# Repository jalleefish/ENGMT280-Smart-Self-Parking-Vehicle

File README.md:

# ENGMT280-Smart-Self-Parking-Vehicle
ENGMT280/ENGEE281 – 25B
Smart Self-parking Vehicle – Design Rules
A scaled version of a typical car park layout will be setup in D.2.03 and C.1.12 (eventually). So
please make sure to feel free to switch lab spaces during the later half of the trimester to have a
go at testing your systems on the track. Below are the design requirements and design constraints
that needs to met by the Smart self-parking vehicle (SSV) you design, while meeting the event
regulations.

Fig. 1(top). Arena for the SSV showing the starting point and the parking bays and (bottom)
Colored tiles placed at the parking bay’s rear wall and parking sensors to check successful vehicle
parking.
ENGMT280/ENGEE281 – 25B
1. Your SAV, once ‘started’, should be able to complete the task autonomously – i.e., no user
inputs from any sort of wired or wireless communication sources once the SSV starts to move.
2. The only form of external communication once your SSV starts is the camera feed going
between the SSV and your laptop/pc for image processing and the processed image’s info
being sent back to the SSV.
3. The SSV, before it’s switched ‘on’, should be completely within the starting area of the arena
(highlighted by the engraved box along the bottom part of the arena in Fig 1(top))
4. There is no restriction for which side can be chosen to start the SSV from as the arena is
symmetric along the vertical axis as seen from Fig 1 (top)’s orientation. The SSV design team
can choose their preferred starting side. If starting from the left-hand side, the SSV needs to
reverse while steering left into parking position and if starting from the right-hand side, the
SSV needs to reverse while steering right back into the parking bay.
5. There will be a reference tile after the starting point where the reference-coloured tile will
be placed that indicates the color of the parking bay that the SSV can park at.
6. The SSV needs to be able to travel along the parking area’s length while checking for available
spots and simultaneously check if that available spot is indeed a valid parking spot.
7. The reference color tile that the SSV needs to scan will be bicolored or single colored
depending on the event.
8. A bi-colored tile indicates that the 2 different spots the SSV should park at in sequence. For
instance if the reference tile is half red and half yellow, the SSV should park in both spots one
after the other in any order.
9. As a minimum requirement, the SSV should atleast be able to park at a single spot (teams can
request a single-colored tile if that’s all they manage to scan and park at). However, marks
will be awarded accordingly.
10. The scoring sheet will be made available on Moodle near the second half of the trimester.
11. The SSV can in no way cause any damage to any part of the arena including the dummy car
models placed in the parked spots.
12. The overall dimensional and dynamic constraints for the SSV are given below
a. Max Length of SSV – 180 mm
b. Max width of SSV – 80 mm
c. Max height of SSV – 75 mm
d. Absolute wheelbase of the SSV – 120 mm
e. The minimum turning radius for the SSV is – 245.346096 mm (represents the half of
the diametrical distance between the outer wheels of the rear axle of the SSV, while
making an exact 180° turn).
f. The SSV shall not have a differential
drive arrangement (not to be confused
with the use of differential gearbox)
where one wheel is driven intentionally
at a rate different from the other wheel
on the same axle that causes the chassis
to pivot with a sharper turning radius
(see Fig 2 for an example of differential
drive robot) Fig.2. Example of a differential drive
robot (which is not allowed)

ENGMT280/ENGEE281 – 25B
g. If the use of some standard parts causes the width of the SSV to be slightly higher than
the allowed SSV width, the teaching team may allow it.
14. All the colored tiles and the reference tile will only be placed after the SSV starts moving.
15. The order of colours tiles placed in the slots will be at random, and their orders will be
changed between each team’s runs.
16. The reference-colored tile will be placed before the SSV reaches the location.

17. The SSVs needs to stop within the correctly identiϐied parking bay’s engraved area and should
not bump the rear walls/colored tiles.
Fig. 2. Rendering showing what the dummy car placements will be like
18. Dummy model cars will also be placed at random creating randomized open parking bays in
the arena.
19. The dummy model cars will not have the same color as the colored tiles that would be
randomly placed to avoid ambiguity.
20. If the randomly chosen reference-color tile has a color that already has the dummy model
cars creating a situation where no valid parking bays are present, the SSV should continue
forward and come to a safe stop within the engraved area opposite to the starting spot.
21. Apart from the batteries provided, no other energy sources can be added to the SSV.
Components like elastic bands and light springs will be considered on a case-by-case basis.
(Make sure to consult before design decisions are made if using such energy storage devices).
22. All SSVs will be inspected to ensure unauthorized items are not present on the system and
they completely comply with all the dimensional and dynamic constraints.
23. SAVs considered unsafe to the users/ spectators/university buildings etc., will be disqualiϐied
at the discretion of the teaching team. Take care to consider H&S risk elements such as sharp
edges, ϐinger traps, electrical shorts, etc., and address them appropriately.
24. A list of available materials will be made available on Moodle under ‘design project resources’
section. Any speciϐic equipment if needed, needs to have prior permission obtained.
25. Under the discretion of the teaching team, 3D printing of parts may be allowed if its within a
volume of 3000 mm3 and merits the shape complexity that cannot be otherwise
manufactured using conventional fabrication approach.
ENGMT280/ENGEE281 – 25B
26. As an optional part, the teams can obtain a vacuformed body shell similar to that of the
dummy model car to put over your design. As such, the teams design should ensure all
electronics are within this envelope. Cut outs can be made on the vacuformed body shell to
allow for uninterrupted operation of any sensors.
27. YOUR SSV SHOULD BE CAPABLE OF ADAPTING TO THE CHANGING LIGHTING CONDITIONS
THROUGHOUT THE DAY ACROSS THE TRIMESTER. Any complaints that the lighting is too
harsh or varying will not be tolerated.
28. You will be given 3 tries to ϐinish your run and the best time of the three runs will be taken
for ϐinal grading.
29. If you have any queries on a speciϐic rule, please reach out for clariϐication. Do not assume
your own interpretation of a rule to be correct and have that as the deciding factor for any
design decisions made if there is any ambiguity in a rule.
Rule updates since ϐirst upload

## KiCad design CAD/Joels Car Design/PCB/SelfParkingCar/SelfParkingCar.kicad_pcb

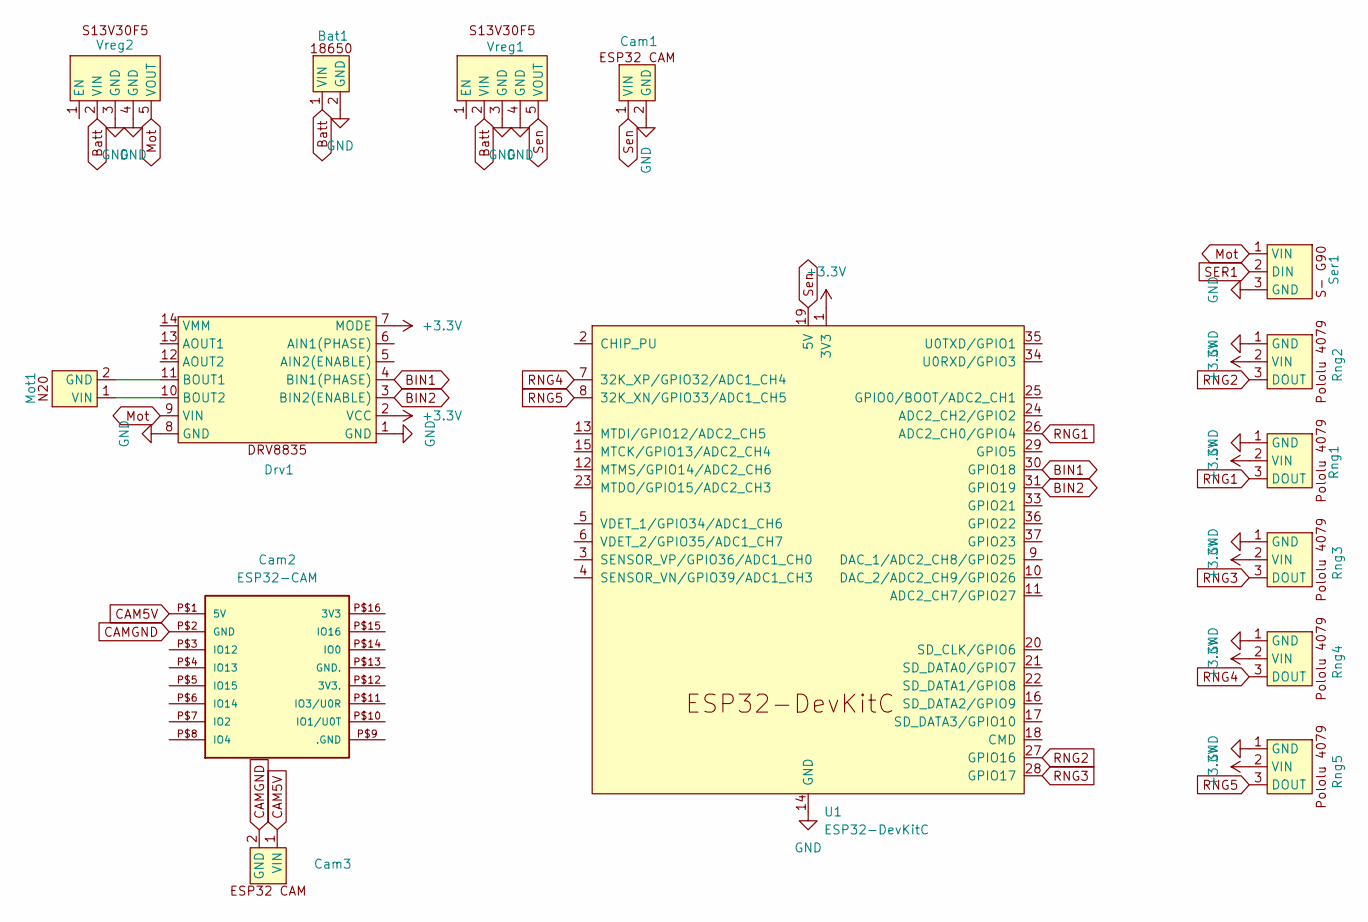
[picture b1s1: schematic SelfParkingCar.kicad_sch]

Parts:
Bat1: 18650 Battery Holder
Cam1, Cam3: ESP32 Camera
Cam2: ESP32-CAM
Drv1: DRV8835 Motor Driver
Mot1: N20 Motor
Rng1, Rng2, Rng3, Rng4, Rng5: Range Sensor
Ser1: S-G90 Servo
U1: ESP32-DevKitC
Vreg1, Vreg2: S13V30F5 Voltage Regulator

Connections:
+3.3V: Drv1.2 (VCC), Drv1.7 (MODE), Rng1.2 (VIN), Rng2.2 (VIN), Rng3.2 (VIN), Rng4.2 (VIN), Rng5.2 (VIN), U1.1 (3V3)
BIN1: Drv1.4 (BIN1(PHASE)), U1.30 (GPIO18)
BIN2: Drv1.3 (BIN2(ENABLE)), U1.31 (GPIO19)
Batt: Bat1.1 (VIN), Vreg1.2 (VIN), Vreg2.2 (VIN)
CAM5V: Cam2.P$1 (5V), Cam3.1 (VIN)
CAMGND: Cam2.P$2 (GND), Cam3.2 (GND)
GND: Bat1.2 (GND), Cam1.2 (GND), Drv1.1 (GND), Drv1.8 (GND), Rng1.1 (GND), Rng2.1 (GND), Rng3.1 (GND), Rng4.1 (GND), Rng5.1 (GND), Ser1.3 (GND), U1.14 (GND), U1.32 (GND), U1.38 (GND), Vreg1.3 (GND), Vreg1.4 (GND), Vreg2.3 (GND), Vreg2.4 (GND)
Mot: Drv1.9 (VIN), Ser1.1 (VIN), Vreg2.5 (VOUT)
unnamed: Drv1.11 (BOUT1), Mot1.2 (GND)
unnamed: Drv1.10 (BOUT2), Mot1.1 (VIN)
RNG1: Rng1.3 (DOUT), U1.26 (ADC2_CH0/GPIO4)
RNG2: Rng2.3 (DOUT), U1.27 (GPIO16)
RNG3: Rng3.3 (DOUT), U1.28 (GPIO17)
RNG4: Rng4.3 (DOUT), U1.7 (32K_XP/GPIO32/ADC1_CH4)
RNG5: Rng5.3 (DOUT), U1.8 (32K_XN/GPIO33/ADC1_CH5)
SER1: Ser1.2 (DIN)
Sen: Cam1.1 (VIN), U1.19 (5V), Vreg1.5 (VOUT)

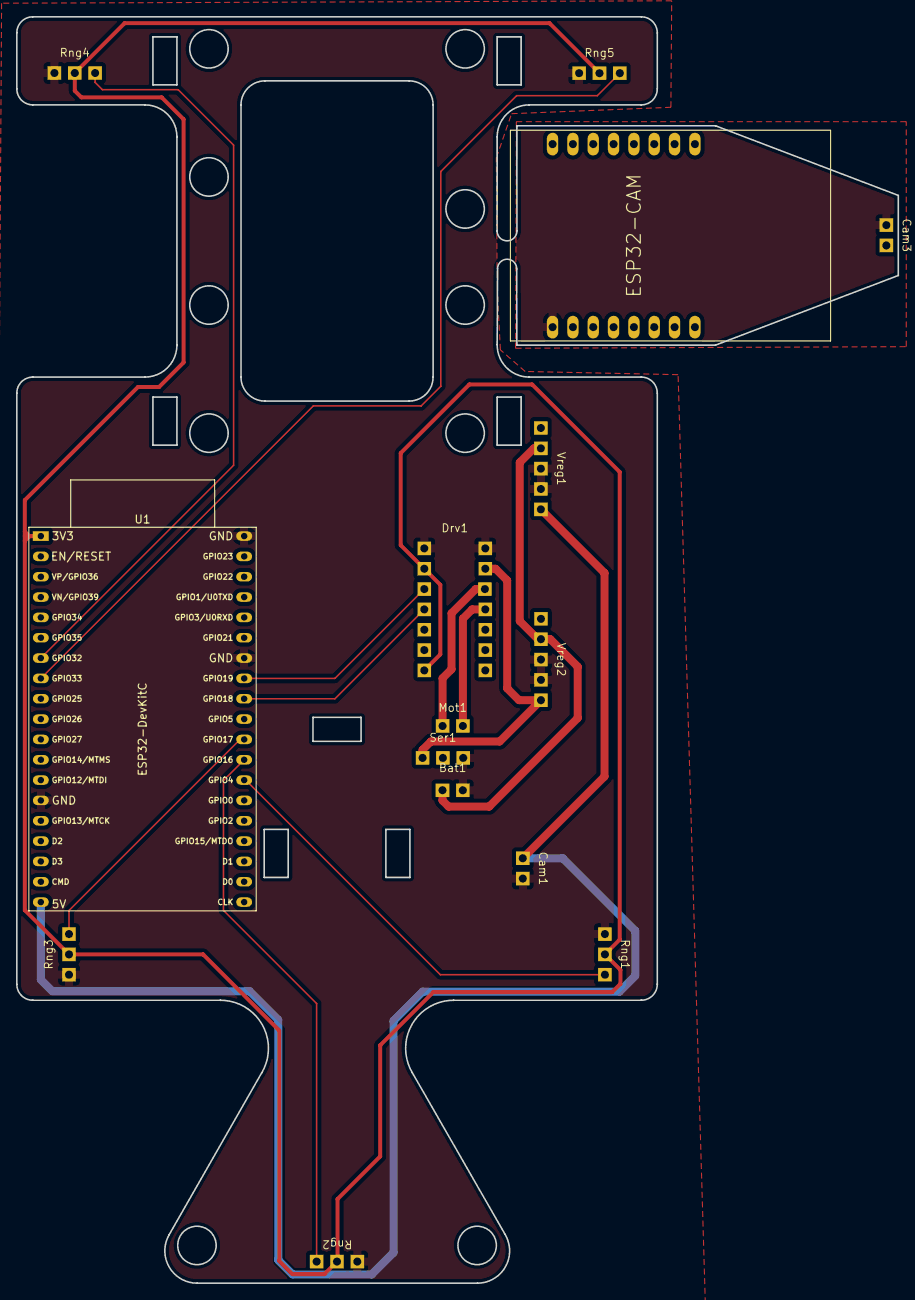
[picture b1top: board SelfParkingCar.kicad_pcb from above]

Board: 2 copper layers, 110.1 x 158.2 mm, 15 parts (0 on the bottom side), 16 nets.

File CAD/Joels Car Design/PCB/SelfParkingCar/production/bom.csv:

Designator,Footprint,Quantity,Value,LCSC Part #
BAT1,18650 Battery Holder,1,~,
"CAM1, CAM3",ESP32 Camera,2,~,
CAM2,ESP32-CAM,1,ESP32-CAM,
DRV1,DRV8835 Motor Driver,1,~,
MOT1,N20 Motor,1,~,
"RNG1, RNG2, RNG3, RNG4, RNG5",Range Sensor,5,~,
SER1,S-G90 Servo,1,~,
U1,ESP32-DevKitC,1,ESP32-DevKitC,
"VREG1, VREG2",S13V30F5 Voltage Regulator,2,~,

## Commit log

2025-07-09 Repository Layout
2025-07-09 ESP32 Code Setup
2025-07-09 CAD Models
2025-07-10 All 3D Models
2025-07-11 Design
2025-07-17 Design Update
2025-07-29 CAD complete, laser cutting setup
2025-07-31 Distance Sensor Code Test
2025-08-01 5 Distance Sensors & Motor Control
2025-08-02 Clean Up
2025-08-03 PCB Design Prototype
2025-08-05 Create Seans Car Design
2025-08-08 PCB Complete
2025-08-12 Code for camera working (unreliable)
2025-08-12 Colour Recognition Working
2025-08-12 PCB Joel's Final Design
2025-09-17 A whole lotta stuff
2025-09-18 More stuff (Wifi working ish)
2025-09-18 sending to python server
2025-09-19 Working Communications & COmmands
2025-09-19 Create simulation
2025-09-22 Added sys code
2025-09-22 Wifi Sucks
2025-09-23 Create car logic
2025-09-23 Organisation
2025-09-23 Sync
2025-09-23 Shit
2025-09-23 Back to Normal
2025-09-24 IT WORKS!!
2025-09-24 Add files via upload
    Python -> C++
2025-09-24 Add files via upload
    System Logic cpp
2025-09-24 Stable
2025-09-24 Comms Working
2025-09-25 SHIT WORKS!!! KInda
2025-09-25 new colour stuff
2025-09-25 More Image Shit
2025-09-25 Better communication
2025-09-25 centre colour logic
2025-09-25 HE DO THE WIBBLE WOBBLE
2025-09-25 TODO List
2025-09-25 TODO
2025-09-25 Straight Driving and better comms
2025-09-25 colour stuff fixed hopefully
2025-09-25 You shall know where stuff is now
2025-09-25 now it fixed
2025-09-25 was an indexing oop, fixed
2025-09-25 commitment issues
2025-09-25 he turn
2025-09-25 Cool
2025-09-25 updated system logic
2025-09-25 next
2025-09-25 idk testing
2025-09-26 updated logic
2025-09-26 oogabooga
2025-09-26 don't know where this came from
2025-09-26 more
2025-09-26 new clock
2025-09-26 Colour Sit
2025-09-29 video capture update
2025-09-30 Camera Working, Needs white bal
2025-09-30 updated vid cap
2025-09-30 pull
2025-09-30 Working park detection, white ballence calibration fix in progress. Needs park logic
2025-10-01 Video capture working woohoo
2025-10-03 Distance Sensors fixed
2025-10-06 Sturglle
2025-10-06 IT PARKS
2025-10-06 Minimum Working model
2025-10-09 Final COde
2025-10-14 Final Code using 2 Parks
2025-10-14 Code for 1 park for EDS
2025-10-15 Yay we done
